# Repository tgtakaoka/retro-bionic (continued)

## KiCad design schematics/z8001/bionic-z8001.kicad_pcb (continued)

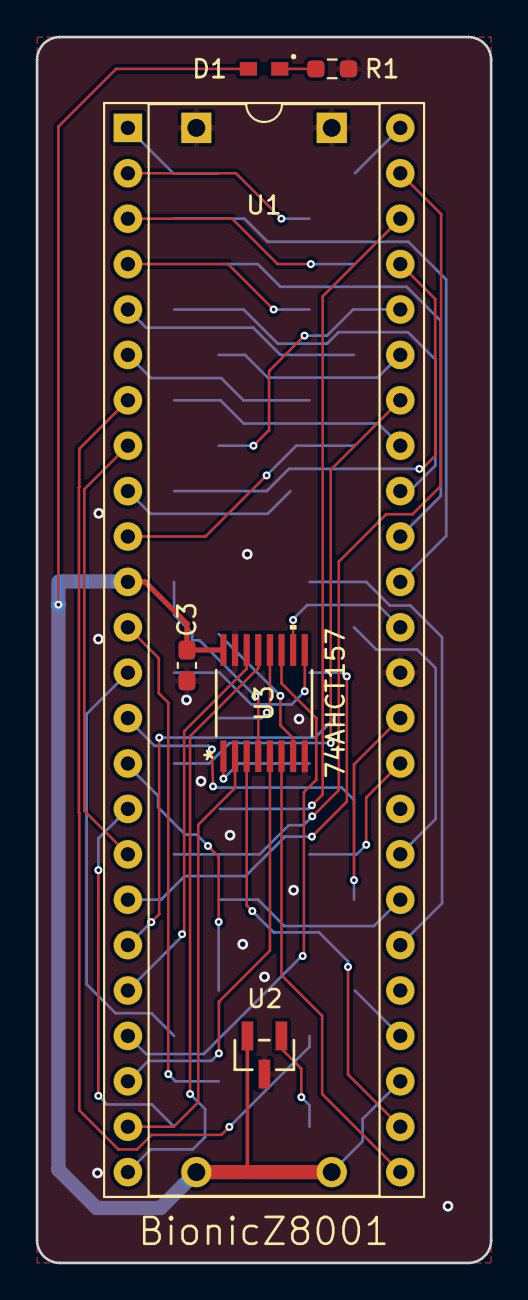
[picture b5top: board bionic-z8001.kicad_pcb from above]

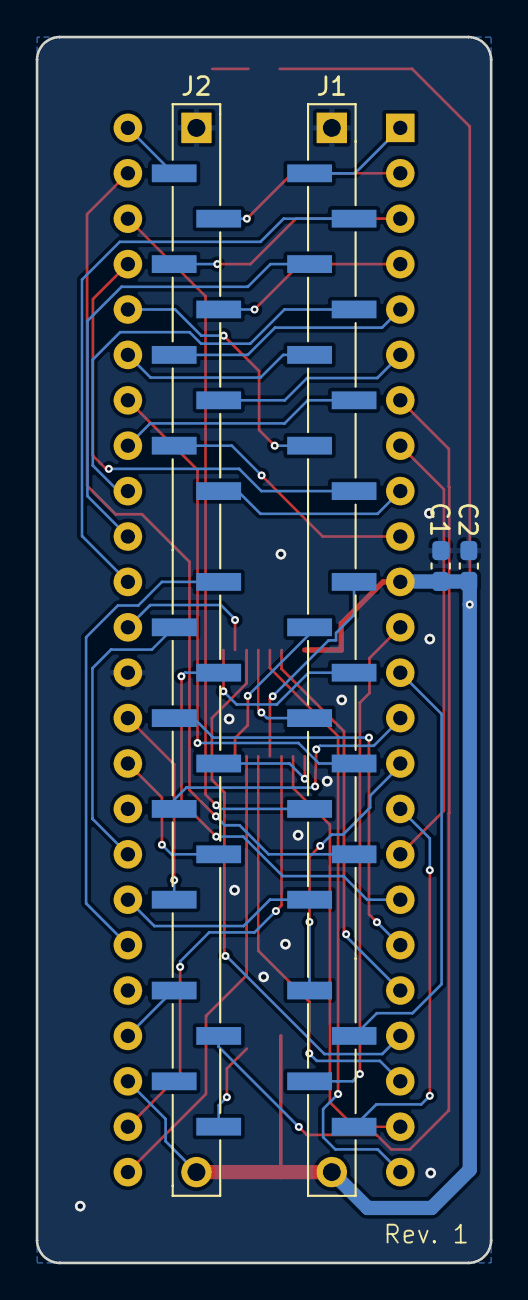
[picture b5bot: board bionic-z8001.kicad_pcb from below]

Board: 2 copper layers, 25.4 x 68.6 mm, 10 parts (4 on the bottom side), 51 nets.

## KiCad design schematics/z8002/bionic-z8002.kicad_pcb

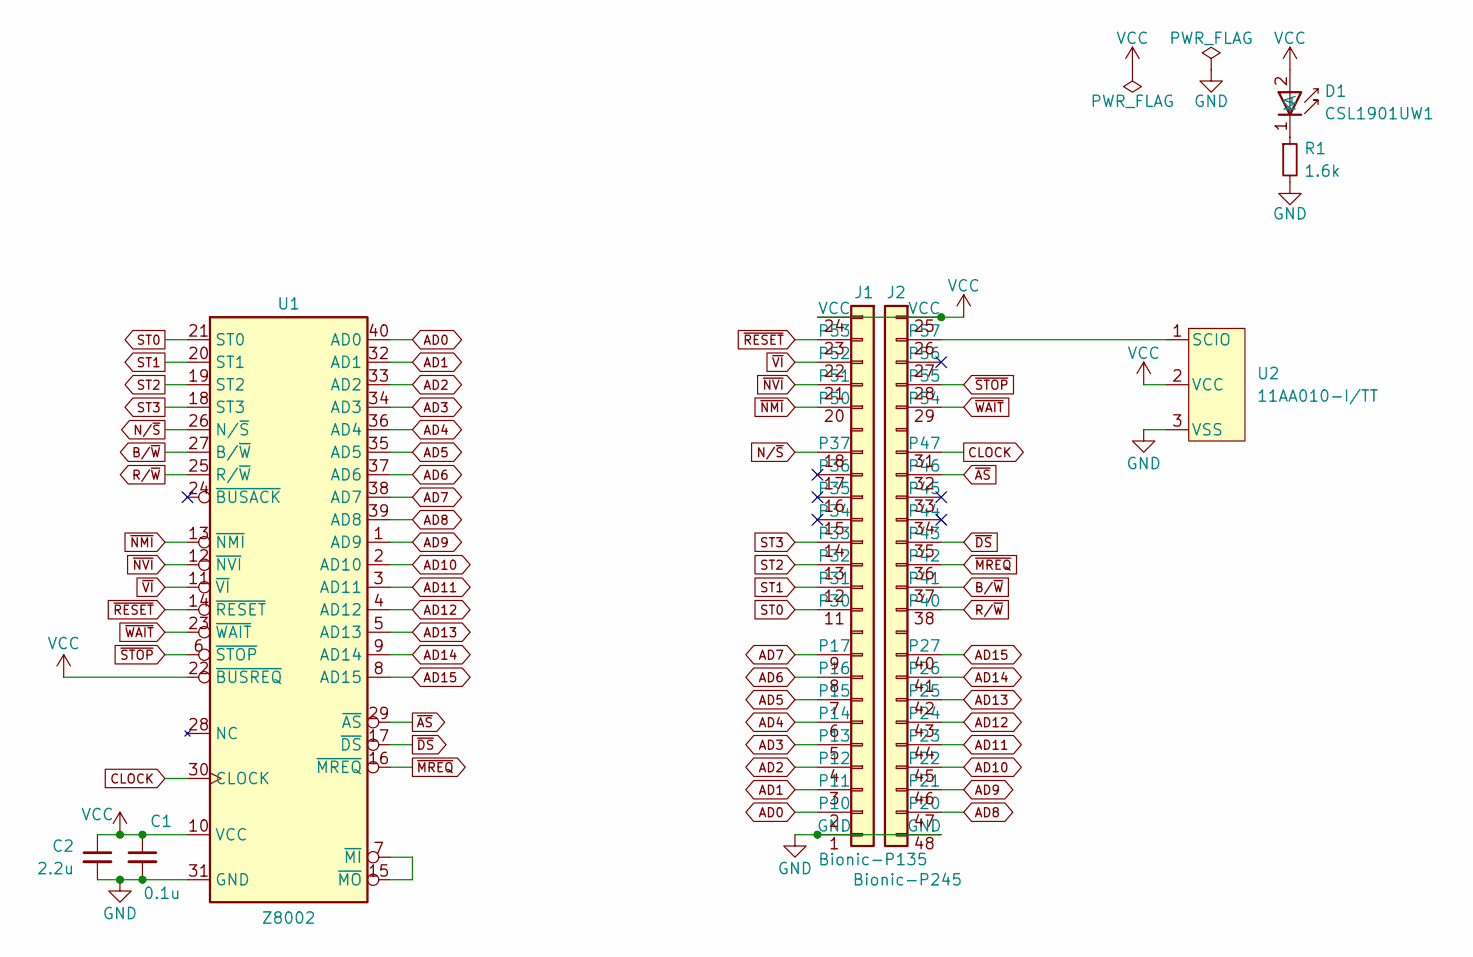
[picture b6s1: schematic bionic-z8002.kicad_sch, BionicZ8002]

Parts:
C1: 0.1u; C_0603_1608Metric_Pad1.08x0.95mm_HandSolder
C2: 2.2u; C_0603_1608Metric_Pad1.08x0.95mm_HandSolder
D1: CSL1901UW1; LED_CSL1901UW1_ROM-M
J1: Bionic-P135; Bionic-P135_THT
J2: Bionic-P245; Bionic-P245_THT
R1: 1.6k; R_0603_1608Metric_Pad0.98x0.95mm_HandSolder
U1: Z8002; DIP-40_W15.24mm_Socket
U2: 11AA010-I/TT; SOT-23_MC_MCH-M

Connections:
AD0: J1.2 (P10), U1.40 (AD0)
AD1: J1.3 (P11), U1.32 (AD1)
AD2: J1.4 (P12), U1.33 (AD2)
AD3: J1.5 (P13), U1.34 (AD3)
AD4: J1.6 (P14), U1.36 (AD4)
AD5: J1.7 (P15), U1.35 (AD5)
AD6: J1.8 (P16), U1.37 (AD6)
AD7: J1.9 (P17), U1.38 (AD7)
AD8: J2.47 (P20), U1.39 (AD8)
AD9: J2.46 (P21), U1.1 (AD9)
AD10: J2.45 (P22), U1.2 (AD10)
AD11: J2.44 (P23), U1.3 (AD11)
AD12: J2.43 (P24), U1.4 (AD12)
AD13: J2.42 (P25), U1.5 (AD13)
AD14: J2.41 (P26), U1.9 (AD14)
AD15: J2.40 (P27), U1.8 (AD15)
B/~W: J2.37 (P41), U1.27 (B/~W)
CLOCK: J2.31 (P47), U1.30 (CLOCK)
GND: C1.2, C2.2, J1.1 (GND), J2.48 (GND), R1.2, U1.31 (GND), U2.3 (VSS)
unnamed: D1.1 (K), R1.1
unnamed: J2.26 (P57), U2.1 (SCIO)
unnamed: U1.7 (~MI), U1.15 (~MO)
N/~S: J1.18 (P37), U1.26 (N/~S)
R/~W: J2.38 (P40), U1.25 (R/~W)
ST0: J1.11 (P30), U1.21 (ST0)
ST1: J1.12 (P31), U1.20 (ST1)
ST2: J1.13 (P32), U1.19 (ST2)
ST3: J1.14 (P33), U1.18 (ST3)
VCC: C1.1, C2.1, D1.2 (A), J1.24 (VCC), J2.25 (VCC), U1.10 (VCC), U1.22 (~BUSREQ), U2.2 (VCC)
~AS: J2.32 (P46), U1.29 (~AS)
~DS: J2.35 (P43), U1.17 (~DS)
~MREQ: J2.36 (P42), U1.16 (~MREQ)
~NMI: J1.20 (P50), U1.13 (~NMI)
~NVI: J1.21 (P51), U1.12 (~NVI)
~RESET: J1.23 (P53), U1.14 (~RESET)
~STOP: J2.28 (P55), U1.6 (~STOP)
~VI: J1.22 (P52), U1.11 (~VI)
~WAIT: J2.29 (P54), U1.23 (~WAIT)

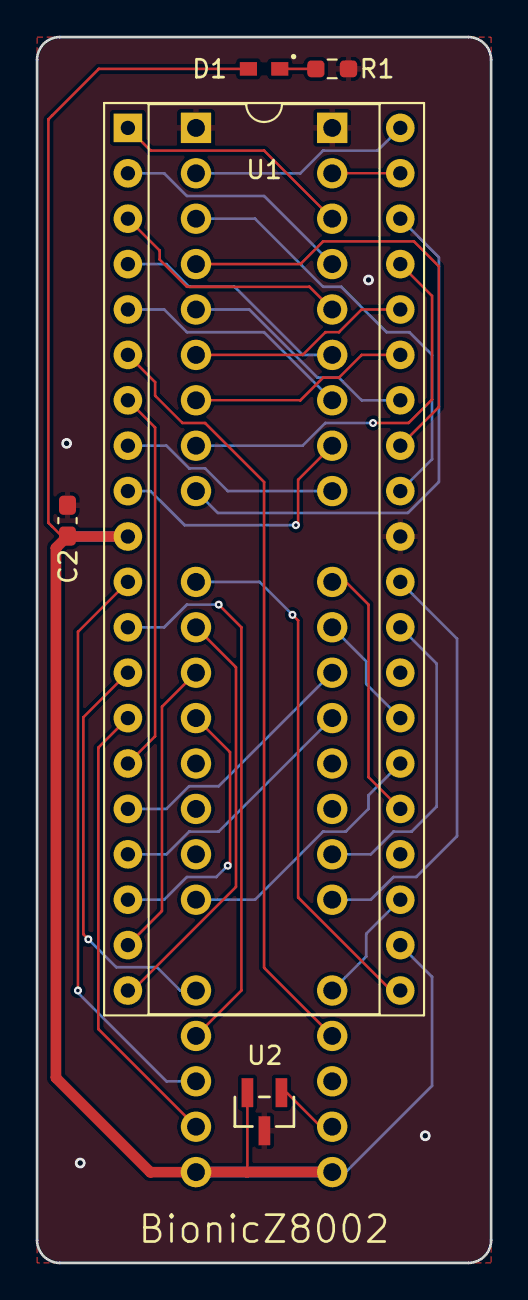
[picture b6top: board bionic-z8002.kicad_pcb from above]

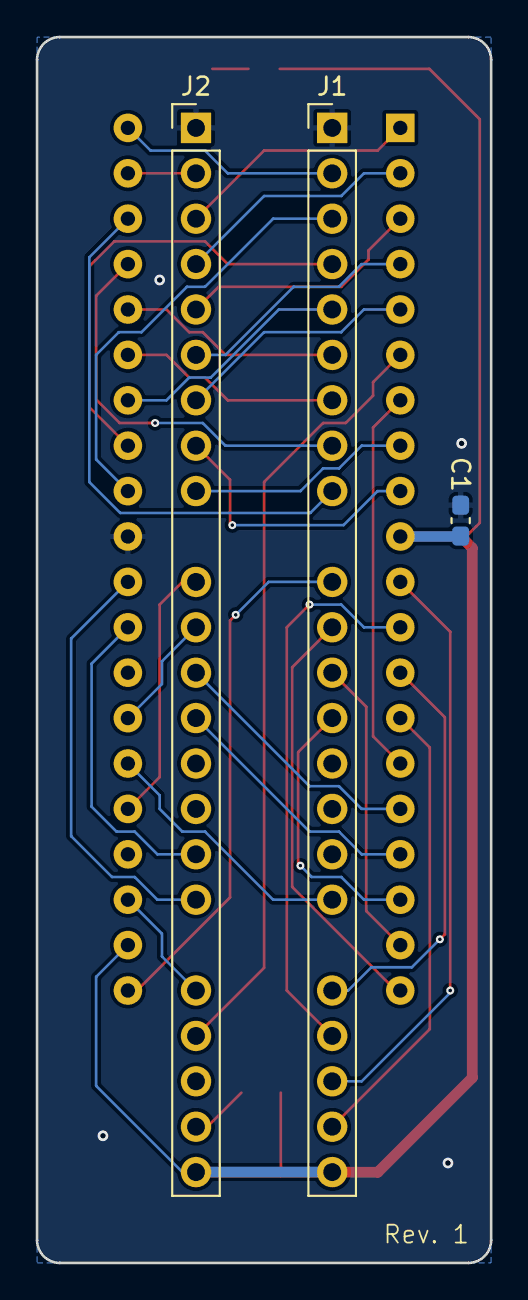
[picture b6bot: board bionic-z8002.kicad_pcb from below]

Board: 2 copper layers, 25.4 x 68.6 mm, 8 parts (3 on the bottom side), 38 nets.

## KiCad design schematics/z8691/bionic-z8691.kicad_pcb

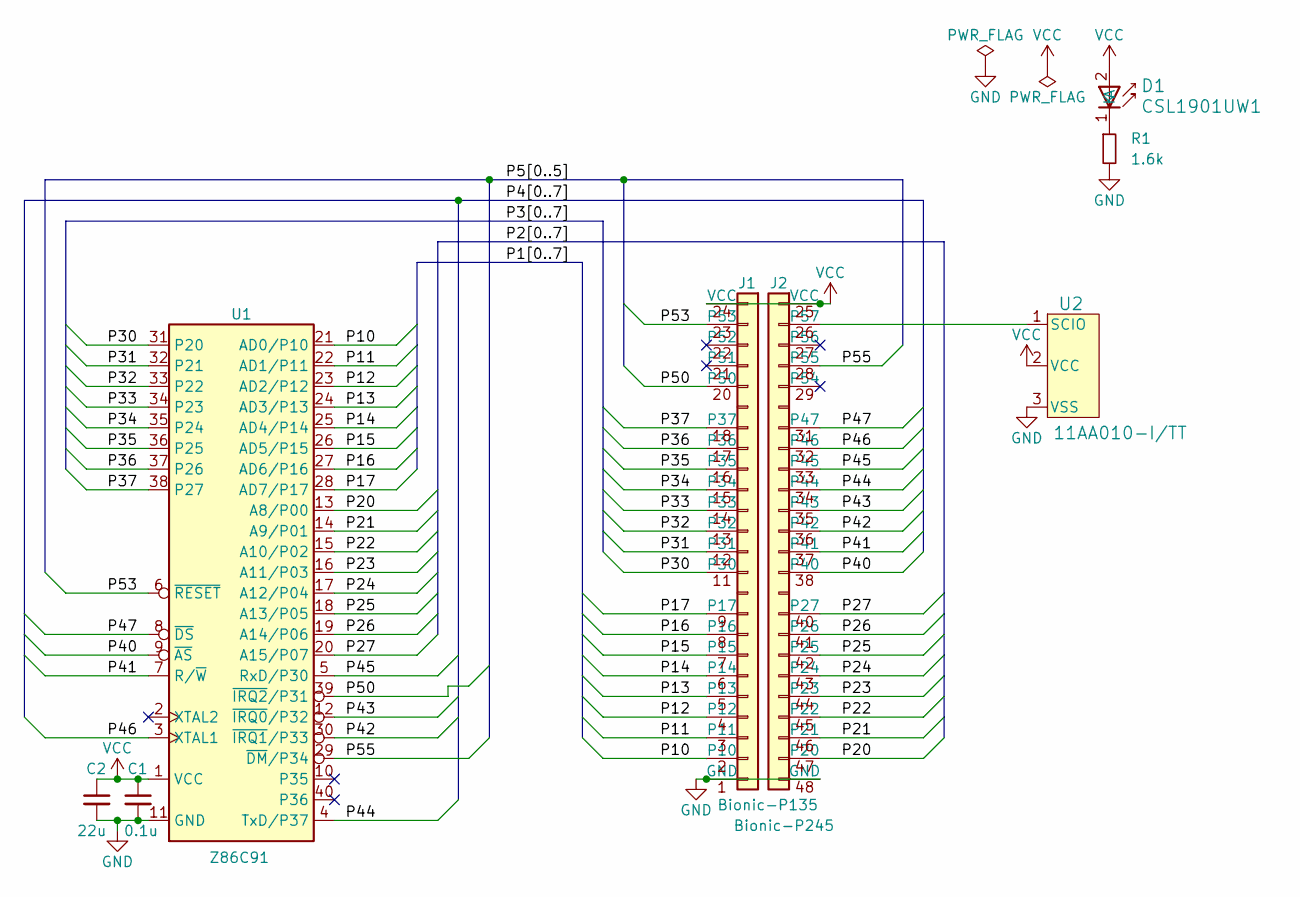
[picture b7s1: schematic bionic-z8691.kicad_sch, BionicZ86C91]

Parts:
C1: 0.1u; C_0603_1608Metric_Pad1.08x0.95mm_HandSolder
C2: 22u; C_0603_1608Metric_Pad1.08x0.95mm_HandSolder
D1: CSL1901UW1; LED_CSL1901UW1_ROM-M
J1: Bionic-P135; Bionic-P135_THT
J2: Bionic-P245; Bionic-P245_THT
R1: 1.6k; R_0603_1608Metric_Pad0.98x0.95mm_HandSolder
U1: Z86C91; DIP-40_W15.24mm_Socket
U2: 11AA010-I/TT; SOT-23_MC_MCH-M

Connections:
/P10: J1.2 (P10), U1.21 (AD0/P10)
/P11: J1.3 (P11), U1.22 (AD1/P11)
/P12: J1.4 (P12), U1.23 (AD2/P12)
/P13: J1.5 (P13), U1.24 (AD3/P13)
/P14: J1.6 (P14), U1.25 (AD4/P14)
/P15: J1.7 (P15), U1.26 (AD5/P15)
/P16: J1.8 (P16), U1.27 (AD6/P16)
/P17: J1.9 (P17), U1.28 (AD7/P17)
/P20: J2.47 (P20), U1.13 (A8/P00)
/P21: J2.46 (P21), U1.14 (A9/P01)
/P22: J2.45 (P22), U1.15 (A10/P02)
/P23: J2.44 (P23), U1.16 (A11/P03)
/P24: J2.43 (P24), U1.17 (A12/P04)
/P25: J2.42 (P25), U1.18 (A13/P05)
/P26: J2.41 (P26), U1.19 (A14/P06)
/P27: J2.40 (P27), U1.20 (A15/P07)
/P30: J1.11 (P30), U1.31 (P20)
/P31: J1.12 (P31), U1.32 (P21)
/P32: J1.13 (P32), U1.33 (P22)
/P33: J1.14 (P33), U1.34 (P23)
/P34: J1.15 (P34), U1.35 (P24)
/P35: J1.16 (P35), U1.36 (P25)
/P36: J1.17 (P36), U1.37 (P26)
/P37: J1.18 (P37), U1.38 (P27)
/P40: J2.38 (P40), U1.9 (~AS)
/P41: J2.37 (P41), U1.7 (R/~W)
/P42: J2.36 (P42), U1.30 (~IRQ1/P33)
/P43: J2.35 (P43), U1.12 (~IRQ0/P32)
/P44: J2.34 (P44), U1.4 (TxD/P37)
/P45: J2.33 (P45), U1.5 (RxD/P30)
/P46: J2.32 (P46), U1.3 (XTAL1)
/P47: J2.31 (P47), U1.8 (~DS)
/P50: J1.20 (P50), U1.39 (~IRQ2/P31)
/P53: J1.23 (P53), U1.6 (~RESET)
/P55: J2.28 (P55), U1.29 (~DM/P34)
GND: C1.2, C2.2, J1.1 (GND), J2.48 (GND), R1.2, U1.11 (GND), U2.3 (VSS)
unnamed: D1.1 (K), R1.1
unnamed: J2.26 (P57), U2.1 (SCIO)
VCC: C1.1, C2.1, D1.2 (A), J1.24 (VCC), J2.25 (VCC), U1.1 (VCC), U2.2 (VCC)

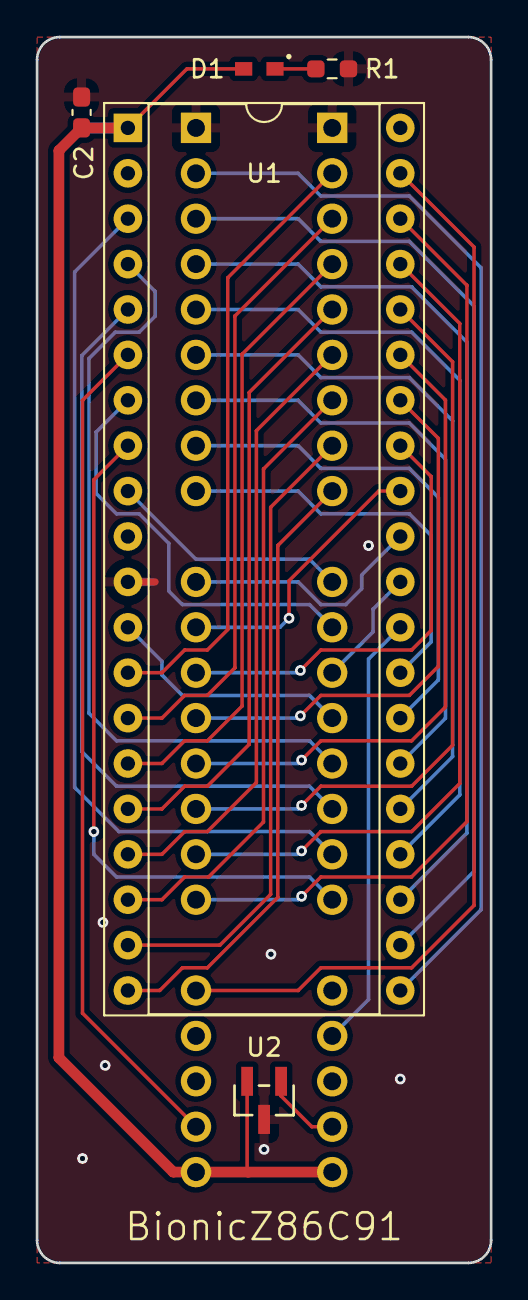
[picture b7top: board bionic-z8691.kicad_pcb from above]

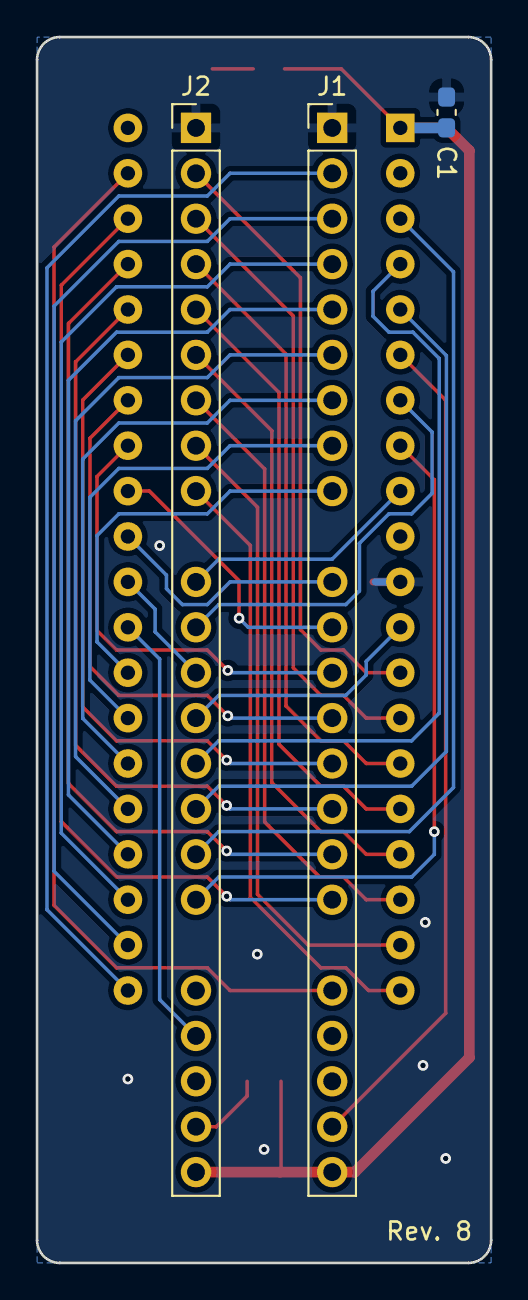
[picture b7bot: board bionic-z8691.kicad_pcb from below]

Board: 2 copper layers, 25.4 x 68.6 mm, 8 parts (3 on the bottom side), 39 nets.
